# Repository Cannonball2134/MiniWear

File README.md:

# MiniWear
MiniWear - Miniature &amp; Wearable Electronics Modules

To see the full details of this project please checkout https://hackaday.io/project/7671-miniwear-diy-miniature-wearable-electronics

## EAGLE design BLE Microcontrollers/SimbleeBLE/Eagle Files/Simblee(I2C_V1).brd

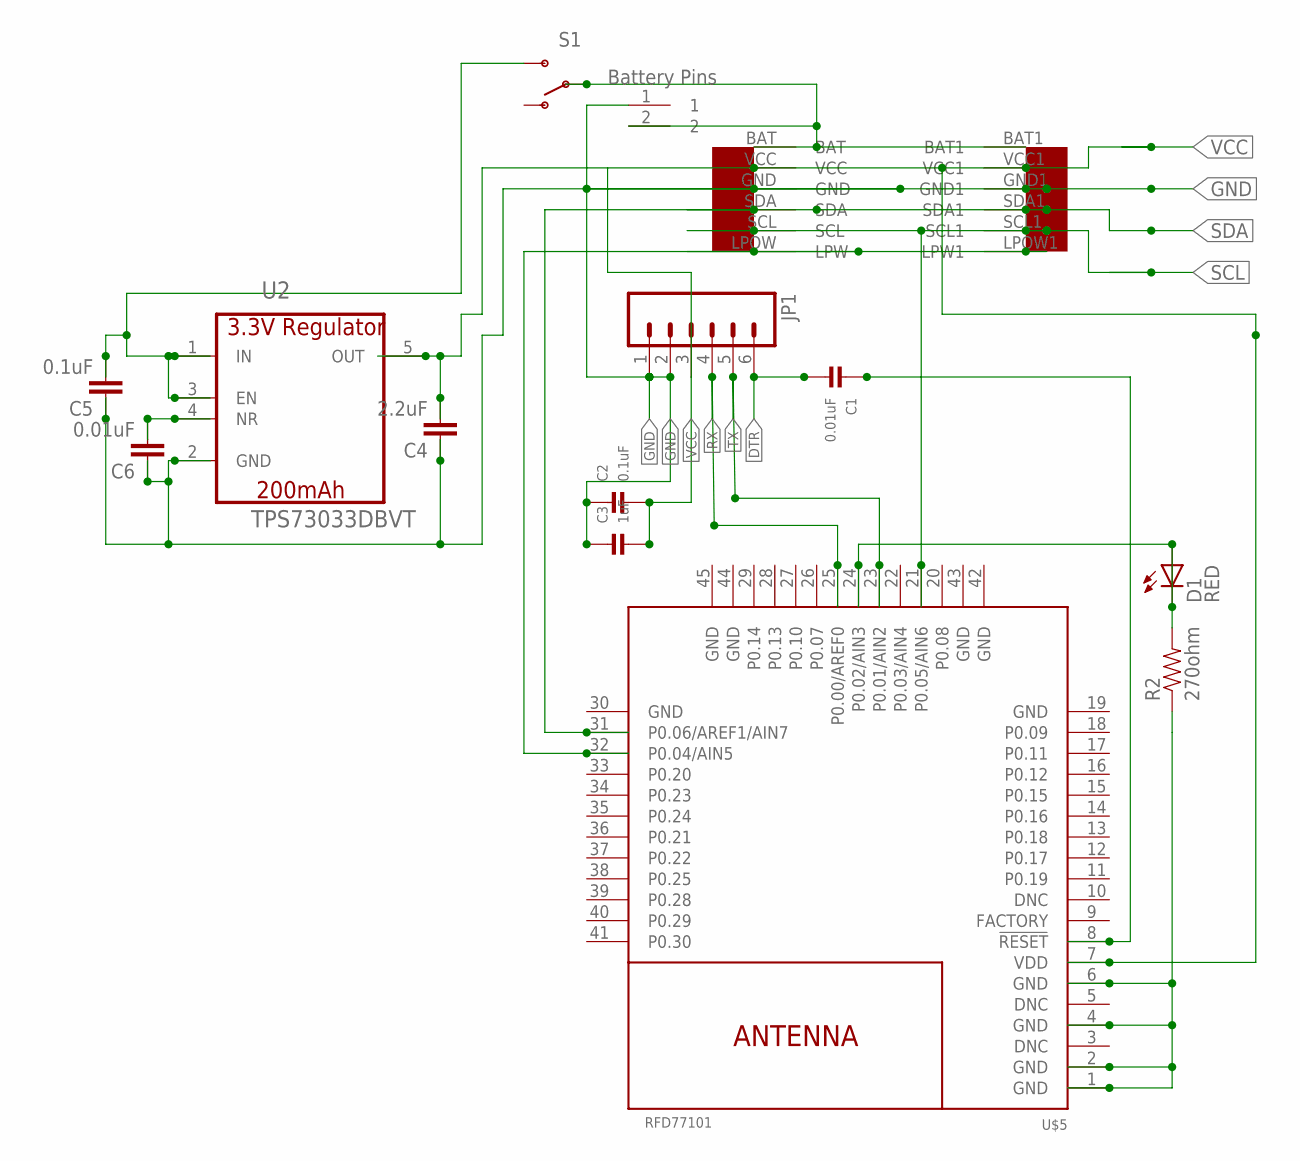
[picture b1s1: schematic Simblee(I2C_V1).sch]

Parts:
BATTERYPINS: MINI_BATTERY_HOLES
C1: 0.01uF; 0402
C2: 0.1uF; 0402
C3: 1uF; 0402
C4: 2.2uF; 0402-CAP
C5: 0.1uF; 0402-CAP
C6: 0.01uF; 0402-CAP
D1: RED; LED-0603
JP1: M06SIP; 1X06
R2: 270ohm; 0402-RES
S1: SWITCH-SPDT-SMD-A; SWITCH-SPST-SMD-A
U2: TPS73033DBVT; SOT95P290X145-5N
U$1: EZ-I2CHEADERV1
U$5: RFD77101

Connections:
BAT: BATTERYPINS.2, S1.2, U$1.BAT, U$1.BAT1
BAT_INPUT: C5.2, S1.3 (S), U2.1 (IN), U2.3 (EN)
DTR: C1.2, JP1.6
GND: BATTERYPINS.1, C2.1, C3.1, C4.1, C5.1, C6.1, JP1.1, JP1.2, R2.1, U2.2 (GND), U$1.GND, U$1.GND1, U$5.1 (GND), U$5.2 (GND), U$5.4 (GND), U$5.6 (GND), U$5.19 (GND), U$5.30 (GND), U$5.42 (GND), U$5.43 (GND), U$5.44 (GND), U$5.45 (GND)
LPW: U$1.LPOW (LPW), U$1.LPOW1 (LPW1), U$5.32 (P0.04/AIN5)
unnamed: C1.1, U$5.8 (!RESET!)
unnamed: D1.A, U$5.24 (P0.02/AIN3)
unnamed: C6.2, U2.4 (NR)
unnamed: D1.C, R2.2
RX: JP1.4, U$5.25 (P0.00/AREF0)
SCL: U$1.SCL, U$1.SCL1, U$5.21 (P0.05/AIN6)
SDA: U$1.SDA, U$1.SDA1, U$5.31 (P0.06/AREF1/AIN7)
TX: JP1.5, U$5.23 (P0.01/AIN2)
VCC: C2.2, C3.2, C4.2, JP1.3, U2.5 (OUT), U$1.VCC, U$1.VCC1, U$5.7 (VDD)

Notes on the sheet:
Battery Pins

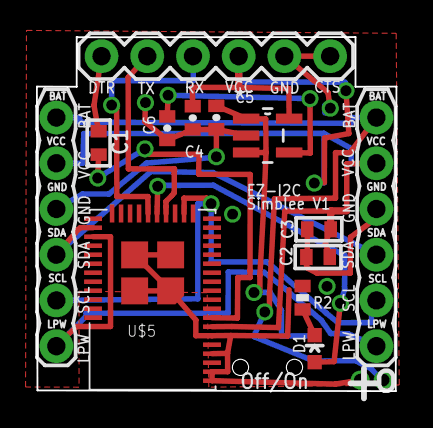
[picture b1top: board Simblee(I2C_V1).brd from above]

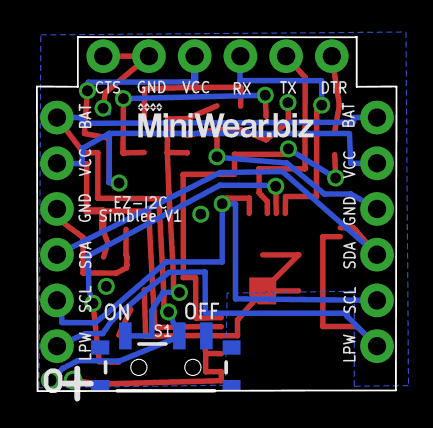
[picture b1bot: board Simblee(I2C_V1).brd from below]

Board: 2 copper layers, 20.0 x 19.7 mm, 15 parts (2 on the bottom side), 14 nets.

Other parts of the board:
U$3: LOGO2

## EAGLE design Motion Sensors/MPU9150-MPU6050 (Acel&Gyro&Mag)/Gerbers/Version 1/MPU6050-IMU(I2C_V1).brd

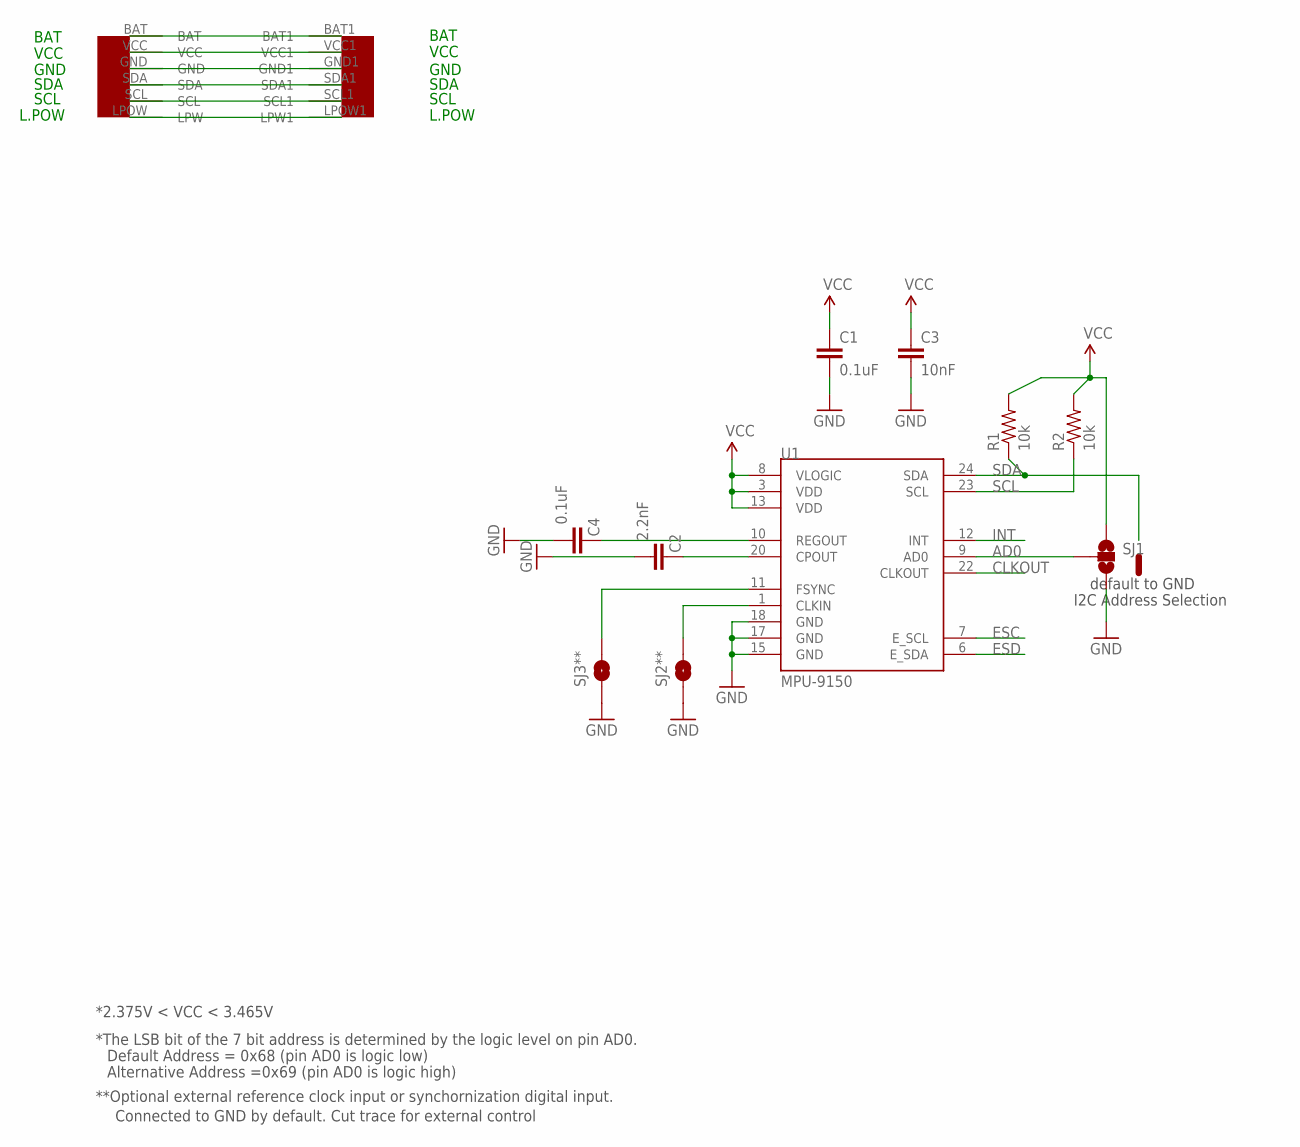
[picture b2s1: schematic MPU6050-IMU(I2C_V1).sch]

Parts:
C1, C4: 0.1uF; 0402-CAP; MPN 02016D104KAT2A
C2: 2.2nF; 0402-CAP; MPN 06035C222KAT2A
C3: 10nF; 0402-CAP; MPN 06035G103ZAT2A
R1, R2: 10k; 0402-RES
SJ1: SOLDERJUMPER_2WAYPASTE2&3; SJ_3_PASTE2&3
SJ2**, SJ3**: SOLDERJUMPERTRACE; SJ_2S-TRACE
U1: MPU-9150; QFN-24-NP
U$1: EASYI2C6PINHEADER

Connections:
AD0: SJ1.2, U1.9 (AD0)
BAT: U$1.BAT, U$1.BAT1
CLKIN: SJ2**.2, U1.1 (CLKIN)
CLKOUT: U1.22 (CLKOUT)
ESC: U1.7 (E_SCL)
ESD: U1.6 (E_SDA)
FSYNC: SJ3**.2, U1.11 (FSYNC)
GND: C1.2, C2.2, C3.2, C4.2, SJ1.3, SJ2**.1, SJ3**.1, U1.15 (GND), U1.17 (GND), U1.18 (GND), U$1.GND, U$1.GND1
INT: U1.12 (INT)
unnamed: C2.1, U1.20 (CPOUT)
unnamed: C4.1, U1.10 (REGOUT)
unnamed: U$1.LPOW (LPW), U$1.LPOW1 (LPW1)
SCL: R2.1, U1.23 (SCL), U$1.SCL, U$1.SCL1
SDA: R1.1, U1.24 (SDA), U$1.SDA, U$1.SDA1
VCC: C1.1, C3.1, R1.2, R2.2, SJ1.1, U1.3 (VDD), U1.8 (VLOGIC), U1.13 (VDD), U$1.VCC, U$1.VCC1

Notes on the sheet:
I2C Address Selection
**Optional external reference clock input or synchornization digital input.
Connected to GND by default. Cut trace for external control
Default Address = 0x68 (pin AD0 is logic low)
Alternative Address =0x69 (pin AD0 is logic high)
*The LSB bit of the 7 bit address is determined by the logic level on pin AD0.
default to GND
*2.375V < VCC < 3.465V
VCC
GND
SDA
SCL
BAT
L.POW

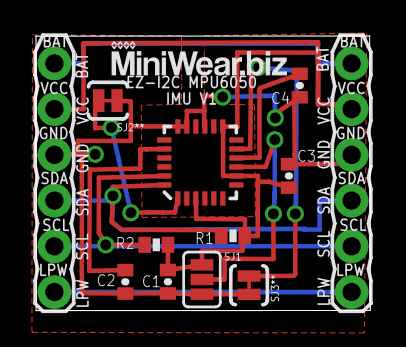
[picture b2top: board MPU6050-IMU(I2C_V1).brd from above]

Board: 2 copper layers, 18.6 x 15.3 mm, 12 parts (0 on the bottom side), 11 nets.

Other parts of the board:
U$2: LOGO2

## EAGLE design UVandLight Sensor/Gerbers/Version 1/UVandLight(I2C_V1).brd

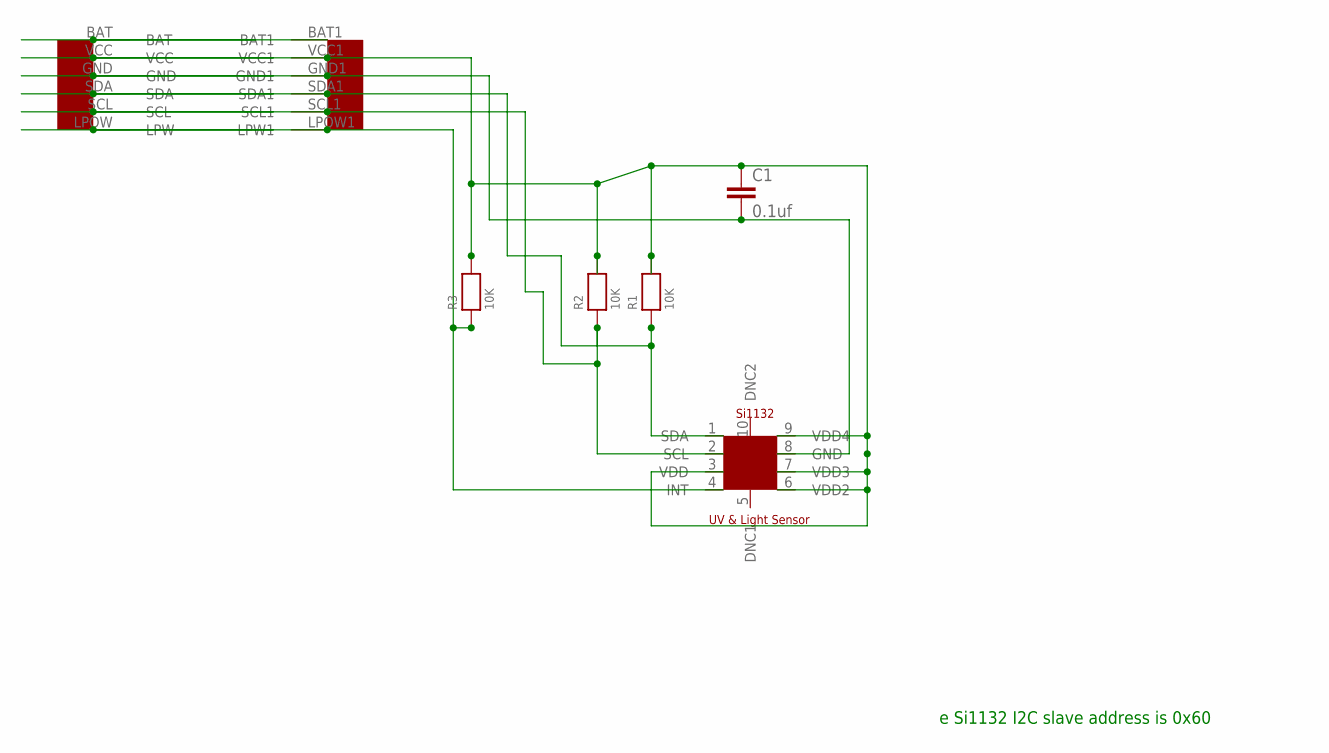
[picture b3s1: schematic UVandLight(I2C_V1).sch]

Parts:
C1: 0.1uf; 0402-CAP
R1, R2, R3: 10K; 0402
U$1: EASYI2C6PINHEADER
U$2: UV-SI1132

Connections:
GND: C1.2, U$1.GND, U$1.GND1, U$2.8 (GND)
unnamed: R1.1, U$1.SDA, U$1.SDA1, U$2.1 (SDA)
unnamed: R3.1, U$1.LPOW (LPW), U$1.LPOW1 (LPW1), U$2.4 (INT)
unnamed: U$1.BAT, U$1.BAT1
unnamed: C1.1, R1.2, R2.2, R3.2, U$1.VCC, U$1.VCC1, U$2.3 (VDD), U$2.6 (VDD2), U$2.7 (VDD3), U$2.9 (VDD4)
unnamed: R2.1, U$1.SCL, U$1.SCL1, U$2.2 (SCL)

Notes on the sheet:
e Si1132 I2C slave address is 0x60

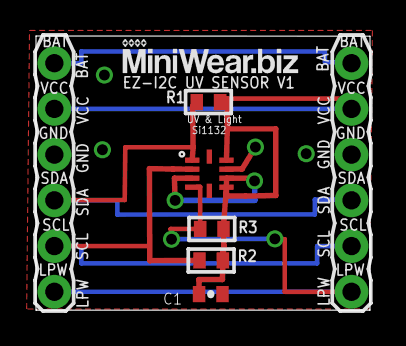
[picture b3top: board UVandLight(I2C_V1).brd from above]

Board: 2 copper layers, 18.6 x 15.2 mm, 7 parts (0 on the bottom side), 6 nets.

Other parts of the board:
U$3: LOGO2

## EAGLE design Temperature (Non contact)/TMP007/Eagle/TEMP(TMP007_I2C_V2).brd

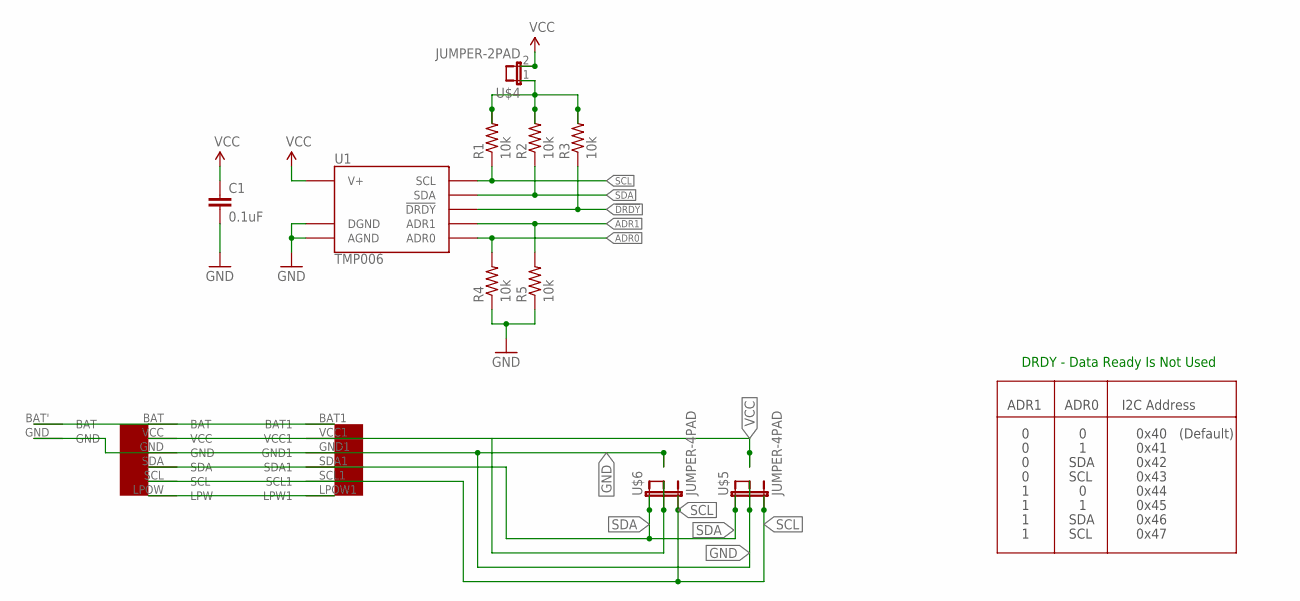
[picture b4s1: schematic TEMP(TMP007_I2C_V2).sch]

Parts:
C1: 0.1uF; 0603-CAP
R1, R2, R3, R4, R5: 10k; 0603-RES
U1: TMP006; BGA8DS
U$1: EZ-I2CHEADERV1
U$3: MINI_BATTERY_HOLES
U$4: JUMPER-2PAD
U$5, U$6: JUMPER-4PAD

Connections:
!DRDY: R3.1, U1.C2 (!DRDY)
ADR0: R4.2, U1.C1 (ADR0)
ADR1: R5.2, U1.B1 (ADR1)
GND: C1.2, R4.1, R5.1, U1.A1 (DGND), U1.A2 (AGND), U$1.GND, U$1.GND1, U$3.GND, U$5.2, U$6.4
unnamed: U$1.BAT, U$1.BAT1, U$3.BAT' (BAT)
unnamed: U$1.LPOW (LPW), U$1.LPOW1 (LPW1)
unnamed: R1.2, R2.2, R3.2, U$4.1
SCL: R1.1, U1.B3 (SCL), U$1.SCL, U$1.SCL1, U$5.3, U$6.3
SDA: R2.1, U1.C3 (SDA), U$1.SDA, U$1.SDA1, U$5.1, U$6.1
VCC: C1.1, U1.A3 (V+), U$1.VCC, U$1.VCC1, U$4.2, U$5.4, U$6.2

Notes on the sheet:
ADR1
ADR0
I2C Address
SDA
SCL
0x40
0x41
0x42
0x43
0x44
0x45
0x46
0x47
(Default)
DRDY - Data Ready Is Not Used

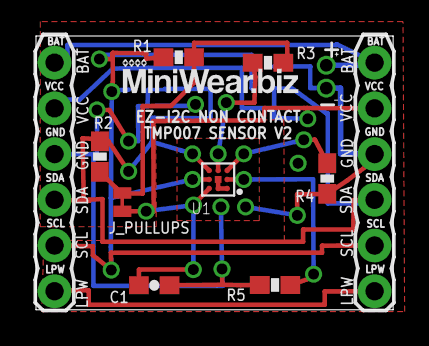
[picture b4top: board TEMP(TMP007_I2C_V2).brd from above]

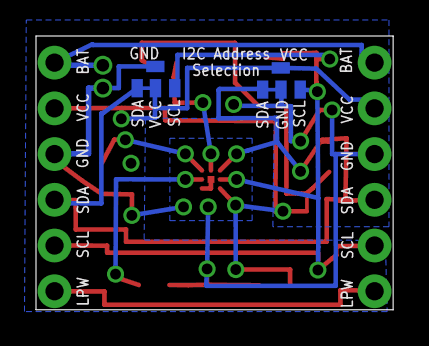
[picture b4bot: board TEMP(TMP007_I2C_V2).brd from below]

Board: 2 copper layers, 19.8 x 15.2 mm, 13 parts (2 on the bottom side), 10 nets.

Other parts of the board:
U$2: LOGO2

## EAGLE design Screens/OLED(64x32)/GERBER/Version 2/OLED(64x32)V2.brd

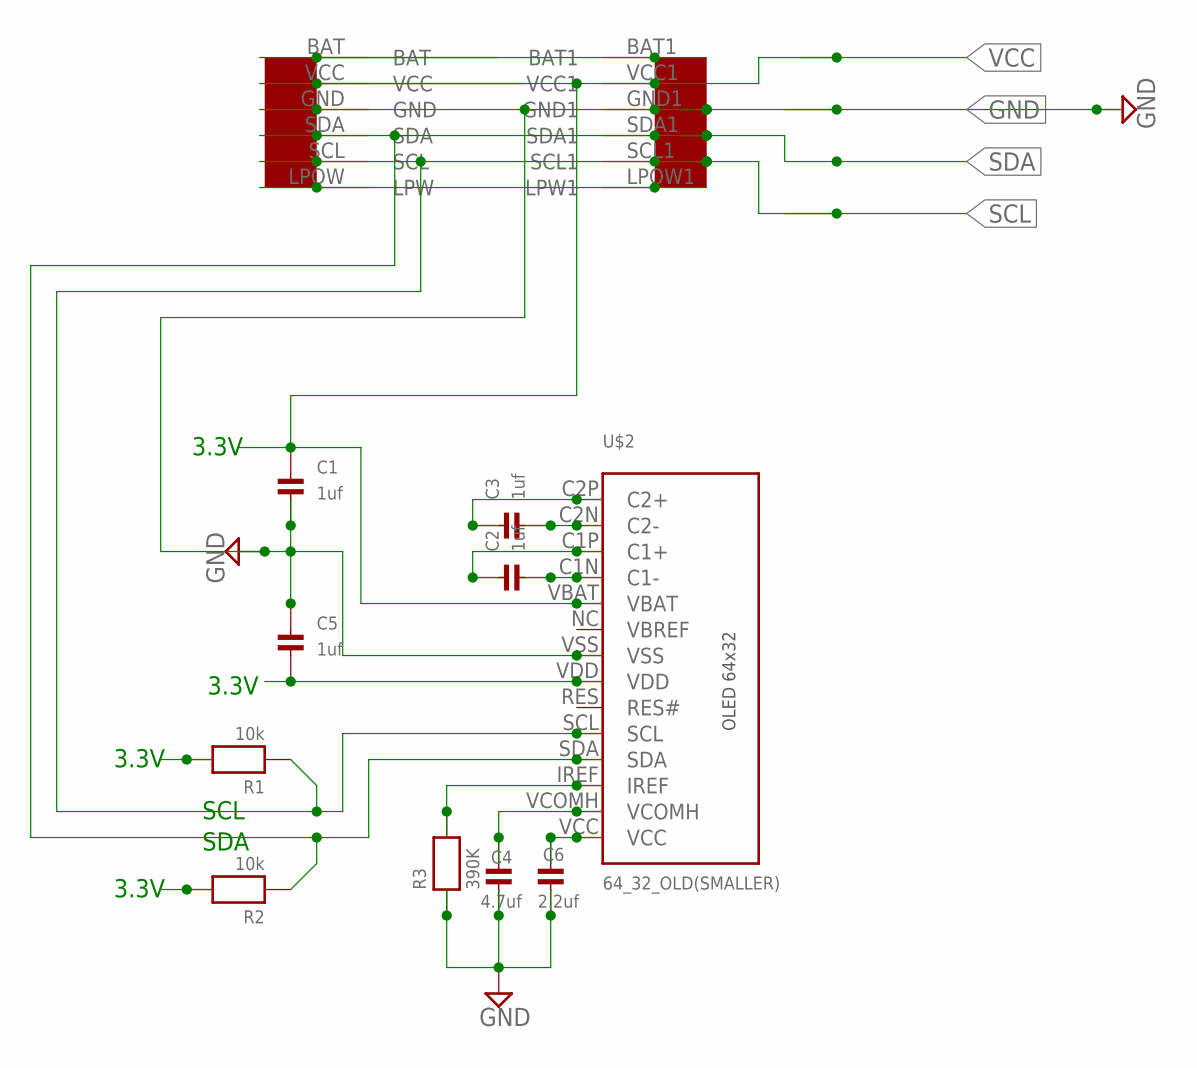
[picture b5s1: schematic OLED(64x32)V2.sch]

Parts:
C1, C2, C3, C5: 1uf; 0603
C4: 4.7uf; 0603
C6: 2.2uf; 0603
R1, R2: 10k; 0603
R3: 390K; 0603
U$1: EZ-I2CHEADERV1
U$2: 64_32_OLD(SMALLER); 62_32_OLED(SMALLER)

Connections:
BAT: U$1.BAT, U$1.BAT1
GND: C1.2, C4.2, C5.1, C6.2, R3.1, U$1.GND, U$1.GND1, U$2.VSS
LPW: U$1.LPOW (LPW), U$1.LPOW1 (LPW1)
unnamed: C2.2, U$2.C1N (C1-)
unnamed: C2.1, U$2.C1P (C1+)
unnamed: C3.2, U$2.C2N (C2-)
unnamed: C3.1, U$2.C2P (C2+)
unnamed: R3.2, U$2.IREF
unnamed: C4.1, U$2.VCOMH
unnamed: C6.1, U$2.VCC
SCL: R1.1, U$1.SCL, U$1.SCL1, U$2.SCL
SDA: R2.1, U$1.SDA, U$1.SDA1, U$2.SDA
VCC: C1.1, C5.2, R1.2, R2.2, U$1.VCC, U$1.VCC1, U$2.VBAT, U$2.VDD

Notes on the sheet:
3.3V
SDA
SCL

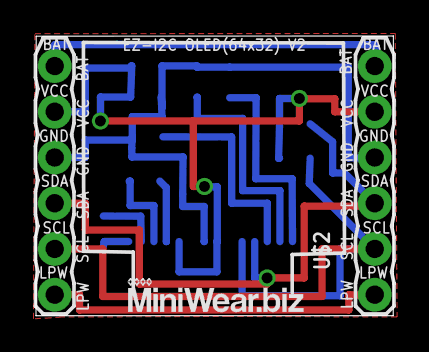
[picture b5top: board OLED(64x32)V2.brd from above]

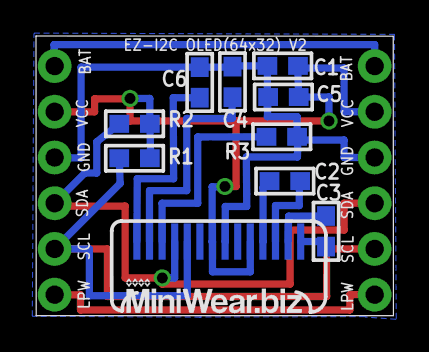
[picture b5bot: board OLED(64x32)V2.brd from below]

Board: 2 copper layers, 19.9 x 15.5 mm, 13 parts (10 on the bottom side), 13 nets.

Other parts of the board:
U$3, U$6: LOGO2

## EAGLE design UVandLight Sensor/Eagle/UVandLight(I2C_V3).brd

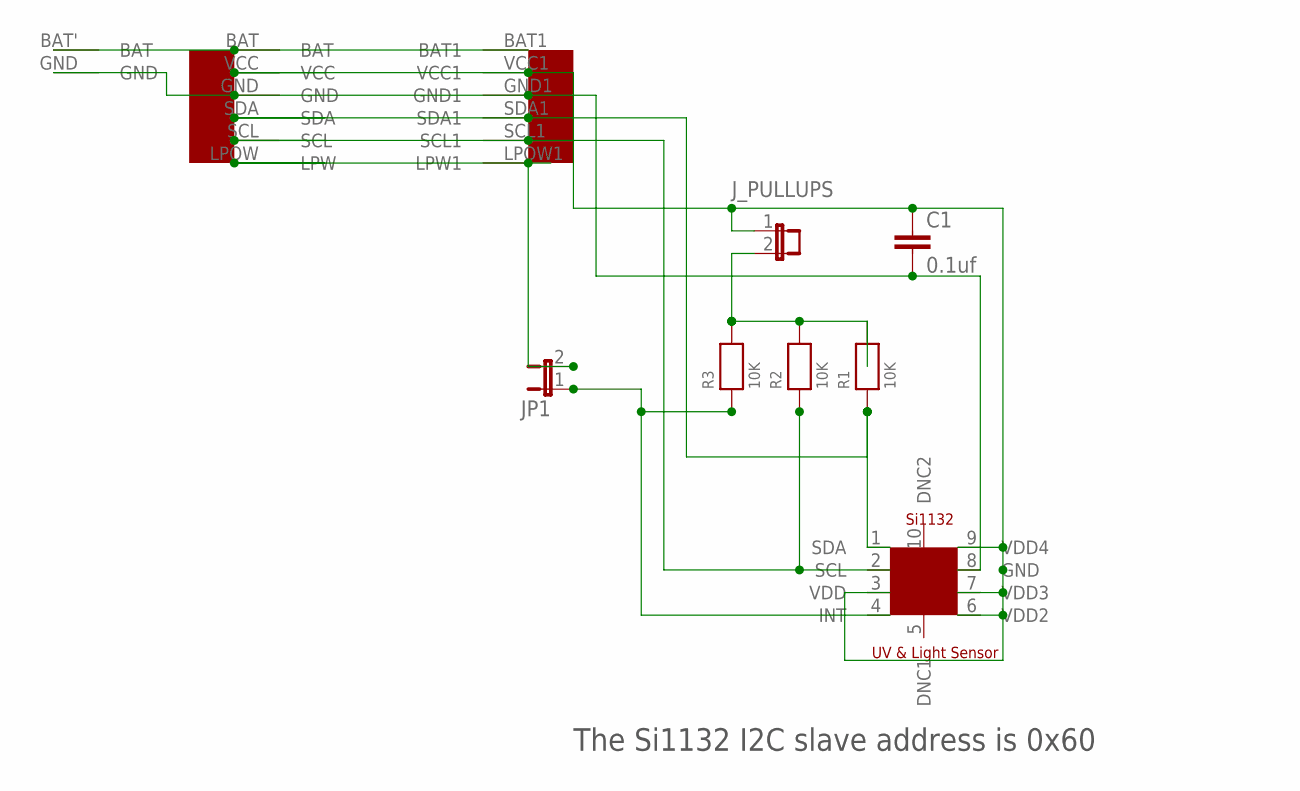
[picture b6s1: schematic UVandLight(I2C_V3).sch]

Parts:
C1: 0.1uf; 0402-CAP
JP1: JUMPER-2SMD-NO-NS; SJ_2S-NO-NS
J_PULLUPS: JUMPER-2PAD
R1, R2, R3: 10K; 0402
U$1: EZ-I2CHEADERV1
U$2: UV-SI1132
U$4: MINI_BATTERY_HOLES

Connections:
GND: C1.2, U$1.GND, U$1.GND1, U$2.8 (GND), U$4.GND
unnamed: R1.1, U$1.SDA, U$1.SDA1, U$2.1 (SDA)
unnamed: JP1.1, R3.1, U$2.4 (INT)
unnamed: U$1.BAT, U$1.BAT1, U$4.BAT' (BAT)
unnamed: JP1.2, U$1.LPOW (LPW), U$1.LPOW1 (LPW1)
unnamed: J_PULLUPS.2, R1.2, R2.2, R3.2
unnamed: C1.1, J_PULLUPS.1, U$1.VCC, U$1.VCC1, U$2.3 (VDD), U$2.6 (VDD2), U$2.7 (VDD3), U$2.9 (VDD4)
unnamed: R2.1, U$1.SCL, U$1.SCL1, U$2.2 (SCL)

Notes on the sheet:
The Si1132 I2C slave address is 0x60

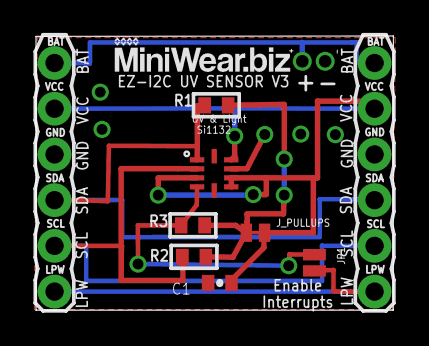
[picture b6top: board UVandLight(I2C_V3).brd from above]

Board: 2 copper layers, 19.9 x 15.2 mm, 10 parts (0 on the bottom side), 8 nets.

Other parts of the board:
U$3: LOGO2

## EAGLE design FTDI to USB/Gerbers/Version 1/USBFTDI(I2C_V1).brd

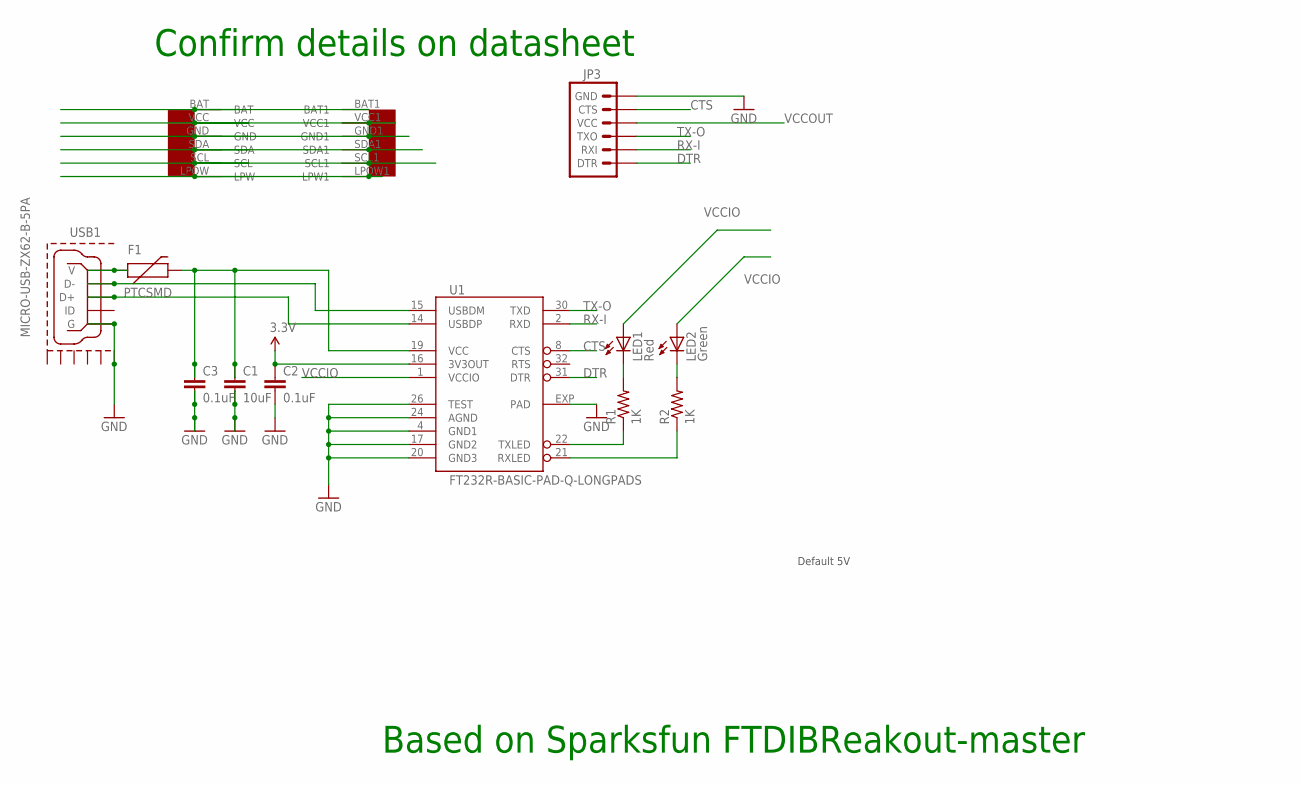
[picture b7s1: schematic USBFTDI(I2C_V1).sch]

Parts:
C1: 10uF; 0402-CAP
C2, C3: 0.1uF; 0402-CAP
F1: PTCSMD; PTC-1206
JP3: ARDUINO_SERIAL_PROGRAMPTH; 1X06
LED1: Red; LED-0603
LED2: Green; LED-0603
R1, R2: 1K; R0402
U1: FT232R-BASIC-PAD-Q-LONGPADS; QFN32-LONG
U$1: EZ-I2CHEADERV1
USB1: MICRO-USB-ZX62-B-5PA; ZX62-B-5PA

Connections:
BAT: U$1.BAT, U$1.BAT1
CTS: JP3.5 (CTS), U1.8 (CTS)
DTR: JP3.1 (DTR), U1.31 (DTR)
GND: C1.2, C2.2, C3.2, JP3.6 (GND), U1.4 (GND1), U1.17 (GND2), U1.20 (GND3), U1.24 (AGND), U1.26 (TEST), U1.EXP (PAD), U$1.GND, U$1.GND1, USB1.5 (G), USB1.GND@6 (GND6)
GND1: USB1.GND@1 (GND1)
GND2: USB1.GND@2 (GND2)
GND3: USB1.GND@3 (GND3)
GND4: USB1.GND@4 (GND4)
GND5: USB1.GND@5 (GND5)
LPW: U$1.LPOW (LPW), U$1.LPOW1 (LPW1)
unnamed: U1.14 (USBDP), USB1.3 (D+)
unnamed: U1.15 (USBDM), USB1.2 (D-)
unnamed: R2.1, U1.21 (RXLED)
unnamed: F1.1, USB1.1 (V)
unnamed: C1.1, C3.1, F1.2, U1.19 (VCC)
unnamed: LED1.C, R1.2
unnamed: LED2.C, R2.2
unnamed: R1.1, U1.22 (TXLED)
RX-I: JP3.2 (RXI), U1.2 (RXD)
SCL: U$1.SCL, U$1.SCL1
SDA: U$1.SDA, U$1.SDA1
TX-O: JP3.3 (TXO), U1.30 (TXD)
VCC: C2.1, U1.16 (3V3OUT), U$1.VCC, U$1.VCC1
VCCIO: LED1.A, LED2.A, U1.1 (VCCIO)
VCCOUT: JP3.4 (VCC)

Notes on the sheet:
Default 5V
Confirm details on datasheet
Based on Sparksfun FTDIBReakout-master

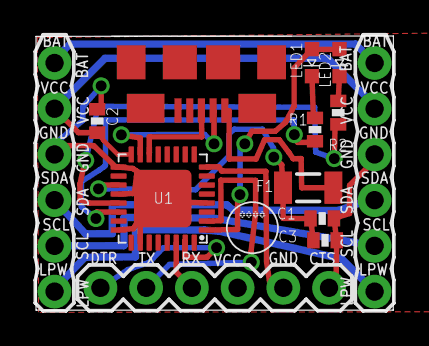
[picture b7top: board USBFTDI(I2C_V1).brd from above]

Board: 2 copper layers, 19.9 x 15.2 mm, 14 parts (1 on the bottom side), 19 nets.

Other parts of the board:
U$2: MLOGO
U$3: LOGO2

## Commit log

2015-11-26 :octocat: Added .gitattributes & .gitignore files
2015-11-26 Schematic and BOM upload
    Added the Eagle files, Gerbers and BOM.
2015-11-26 Added Eagle And Gerber Design Files
2015-11-26 More Gerber and Eagle Files
2016-01-15 Simblee (V1)
    An upgraded MiniWear BLE module that used the Simble IC
2016-09-28 DA14580
    Testing out the Murata LBCA2HNZYZ pre-certified module that uses the
    DA14580. This board was made with KiCad.
2016-09-28 README
    Basic instructions on how to setup up for programming.

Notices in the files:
parts and their libraries:
SparkFun-Connectors: Licensing: CC v3.0 Share-Alike You are welcome to use this library for commercial purposes.
microbuilder: This work is placed in the public domain, and may be freely used for commercial and non-commercial work with the following conditions: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
